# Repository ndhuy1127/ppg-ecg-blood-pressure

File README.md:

# Thiết bị đeo cổ tay ước lượng biến thiên huyết áp từ PPG và ECG

**Thành viên mới:** đọc [Quy trình làm việc GitHub](docs/WORKFLOW.md) trước khi tạo commit hoặc Pull Request.

## Mục tiêu

Dự án xây dựng nguyên mẫu thiết bị đeo cổ tay và pipeline phân tích nhằm nghiên
cứu khả năng ước lượng biến thiên huyết áp giữa các phiên đo từ tín hiệu PPG và
ECG. Sản phẩm hiện chỉ phục vụ nghiên cứu, không phải thiết bị y tế và không
được dùng để chẩn đoán hay đưa ra quyết định điều trị.

## Câu hỏi nghiên cứu

Chi tiết trong
[docs/research_questions_v0.1.md](docs/research_questions_v0.1.md):

1. **RQ1 (câu hỏi chính):** Sau khi hiệu chuẩn bằng một lần đo cuff, việc bổ
   sung ECG để tính PAT có làm giảm sai số dự đoán ΔSBP và ΔDBP ở các phiên đo
   sau so với mô hình chỉ dùng PPG hay không?
2. **RQ2:** Sai số thay đổi bao nhiêu khi chuyển từ chia ngẫu nhiên theo cửa sổ
   (có rò rỉ dữ liệu) sang chia theo người và chia theo phiên đo?
3. **RQ3:** Từ chối dự đoán dựa trên SQI và độ bất định có cho sai số thấp hơn
   so với từ chối ngẫu nhiên ở cùng tỷ lệ giữ lại (coverage) không?

Trong dự án này, **PAT (Pulse Arrival Time)** là thời gian từ đỉnh R của ECG đến
chân sóng PPG. PAT gồm cả thời gian tiền tống máu (PEP), `PAT = PEP + PTT`, nên
**không được gọi là PTT**.

## Thành viên và trách nhiệm

| Thành viên | Trách nhiệm |
| --- | --- |
| Linh | Phần mềm, dữ liệu, mô hình, kiểm thử và CI |
| Đức Anh | Phần cứng, firmware, BOM, PCB và kiểm thử thiết bị |
| Huy | Xử lý tín hiệu, PAT, thống kê, protocol, tài liệu và bài báo |

Phân công chi tiết xem [docs/TEAM.md](docs/TEAM.md).

## Cấu trúc repository

- **configs/**: cấu hình dữ liệu, phần cứng và mô hình.
- **data/**: hướng dẫn quản lý dữ liệu và dữ liệu mẫu nhỏ đã ẩn danh.
- **docs/**: quy trình, kế hoạch, tài liệu nghiên cứu, protocol và đạo đức.
- **hardware/**: BOM, datasheet, sơ đồ nguyên lý, PCB, cơ khí và báo cáo thử.
- **firmware/**: ứng dụng nhúng, driver, board, header và kiểm thử.
- **software/**: nhập dữ liệu, tiền xử lý, xử lý tín hiệu, đặc trưng, mô hình,
  đánh giá và triển khai.
- **notebooks/**: khám phá dữ liệu và thí nghiệm có thể tái lập.
- **scripts/**: công cụ kiểm tra và tác vụ hỗ trợ.
- **tests/**: kiểm thử tự động.
- **reports/**: báo cáo tuần, hình và bản thảo bài báo.

## Cài đặt môi trường

Bắt buộc dùng **Python 3.11**: `pyproject.toml` khai báo
`requires-python = ">=3.11,<3.12"` và CI chạy Python 3.11. Có thể dùng một
trong hai cách:

### pip

Windows PowerShell (`py -3.11` chọn đúng Python 3.11 khi máy có nhiều bản):

~~~powershell
py -3.11 -m venv .venv
.\.venv\Scripts\Activate.ps1
python -m pip install --upgrade pip
python -m pip install -r requirements.txt
~~~

Linux/macOS:

~~~bash
python3.11 -m venv .venv
source .venv/bin/activate
python -m pip install --upgrade pip
python -m pip install -r requirements.txt
~~~

### Conda

~~~text
conda env create -f environment.yml
conda activate ppg-ecg-env
~~~

`requirements.txt`, `pyproject.toml` và `environment.yml` cố định phiên bản
`mat73==0.65` (reader PulseDB), `h5py==3.16.0` (đọc từng phần file `.mat` v7.3, thêm
2026-10-24), `pyserial==3.5` (logger đọc cổng serial, thêm 2026-10-24) và
`xgboost==3.2.0` (baseline B3). PyTorch chưa có
trong dependency; thành viên cần dùng sẽ bổ sung kèm phiên bản cố định.

## Chạy kiểm tra

Từ thư mục gốc của repository, sau khi kích hoạt môi trường:

~~~text
ruff check .
pytest -q
python scripts/check_environment.py
python -m pip check
~~~

## Quy trình nhánh

Luồng tích hợp:

~~~text
dev/thanh-vien → develop → main
~~~

Mỗi người đồng bộ từ **develop**, làm việc trên nhánh cá nhân, tạo pull request
vào **develop** và chờ CI thành công. Chỉ tích hợp **develop** vào
**main** tại một mốc ổn định. Không làm việc trực tiếp trên **main**.

## Dữ liệu và bảo mật

Không commit dữ liệu ECG/PPG thật, dữ liệu định danh, dữ liệu nghiên cứu dung
lượng lớn, bí mật, token hay tệp môi trường. Chỉ dữ liệu mẫu nhỏ và đã ẩn danh
được phép đặt trong **data/sample/**. Dữ liệu nghiên cứu phải dùng
**subject_id**, **session_id** và **event_id**. Xem
[docs/DATA_POLICY.md](docs/DATA_POLICY.md) trước khi thêm dữ liệu.

## Trạng thái dự án

Dự án đang ở tuần 7 trong lộ trình 28 tuần (bắt đầu 2026-09-17; cập nhật 2026-11-10). Tóm tắt theo mức bằng chứng:

| Mức | Nội dung |
| --- | --- |
| Có code và test cục bộ (dữ liệu giả lập) | Reader PulseDB; inventory và split theo người `pulsedb-split-v2`; baseline hằng số B0/B1; MAE/bias/SD; đặc trưng PPG/HR/PAT, SQI `features-sqi-v1` và bootstrap theo người (Tuần 4); pipeline B0/B3 (XGBoost, đặc trưng `pulsedb-simple-stats-v0`) trên split v2, fit trên train và chỉ chấm val ([hướng dẫn](docs/protocol/run_b3_pulsedb.md)); logger packet V0.1 và V0.2 (mốc `SAMP` bit 8, nhiệt độ `0xB1`, cấu hình AFE `0xD2`, lệnh và xác nhận `0xD3`, kênh im lặng), mô phỏng `synthetic-packet-v3`, mốc R/foot thứ hai và quy tắc PAT hợp lệ (Tuần 5) |
| Build được, chưa chạy trên bo | Firmware ESP32-S3 gửi packet V0.2 (`0xD1`, IMU, mốc `SAMP`, nhiệt độ `0xB1`, cấu hình AFE `0xD2`, lệnh từ PC, xung kích thích đồng bộ) từ nguồn AFE giả, và driver chip thật MAX30001, MAX30101, BMI270 chưa chạy trên chip ([firmware/](firmware/README.md)) |
| Đã chạy sơ bộ trên dữ liệu công khai | B0 trên CSV nhãn PulseDB 1.000 đoạn (Tuần 3, lịch sử: tập AAMI Cal đã lộ test, xem [hướng dẫn](docs/protocol/run_b0_pulsedb_csv.md)); B0/B3 trên PulseDB VitalDB Train 400 người, chỉ chấm val, nhãn ABP công khai, không phải cuff ([Tuần 5](reports/weekly/week_05/pulsedb_b3_v1/README.md)); B2 v1 (nhân khẩu học, và thêm HR từ đỉnh R của ECG; [định nghĩa B2](docs/protocol/b2_pulsedb_definition.md)) trên cùng split, chỉ chấm val ngày 2026-11-07, chưa thấy khác biệt so với B0 ([Tuần 6](reports/weekly/week_06/pulsedb_b2_v1/README.md)); B3 chạy ba seed cho cùng kết quả ([theo dõi thí nghiệm](reports/weekly/week_06/experiment_tracking/README.md)). Chưa chấm test |
| Bản thảo | Câu hỏi nghiên cứu, protocol v0.3 ([protocol_outline_v0.2.md](docs/protocol/protocol_outline_v0.2.md)), hồ sơ đạo đức (các mục thiết kế/đạo đức đã có phương án của nhóm ngày 2026-10-29, chờ thầy duyệt trước khi nộp), tổng quan tài liệu, danh sách mua |
| Phần cứng V1, chưa có trong tay | Thiết kế KiCad V1-draft5: PCB V1 đang đặt gia công ở CXT từ 2026-10-28. Bo Waveshare ESP32-S3-DEV-KIT-N8R8-M đã đặt 2026-10-27; các đơn còn lại (DigiKey, kit MAX30001, điện cực, cáp) được báo đã đặt ngày 2026-11-07, ngày giao chưa ghi ([báo cáo Tuần 6](reports/weekly/week_06/README.md)) |
| Chưa có | Phần cứng lắp ráp, bản ghi ECG/PPG của nhóm, dữ liệu cuff, mô hình ΔBP và mọi kết quả trả lời RQ1–RQ3 |

Kết quả trên dữ liệu giả lập chỉ kiểm tra code, không phải hiệu năng ước lượng
huyết áp. Kế hoạch từng tuần nằm trong [docs/plans/](docs/plans/README.md); trạng
thái và bằng chứng nằm trong báo cáo tuần tại [reports/weekly/](reports/weekly/).

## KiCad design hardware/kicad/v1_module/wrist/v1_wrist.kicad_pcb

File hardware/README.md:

# Phần cứng

- **bom/**: danh mục linh kiện và phương án thay thế;
  [danh sách mua V1-module](bom/purchase_list_v1_module.md).
- **datasheets/**: liên kết datasheet chính thức và mức độ đối chiếu thông số
  ([README](datasheets/README.md)); không lưu file PDF.
- **kicad/**: thiết kế KiCad của V1-module, gồm `kicad/v1_module/base` (bo đế)
  và `kicad/v1_module/wrist` (bo cổ tay), mỗi bo có `.kicad_sch`, `.kicad_pcb`,
  `.kicad_pro`. PCB lưu theo định dạng KiCad 10.0, schematic theo 9.0: mở
  `.kicad_pcb` bằng KiCad ≥ 10. Mô tả, bảng GPIO và bảng chân cáp:
  [custom_board_proposal.md](../configs/hardware/custom_board_proposal.md) Phần A.
- **schematics/**: sơ đồ nguyên lý và bản xuất; hiện chỉ có `.gitkeep`.
- **pcb/**: nguồn thiết kế PCB; output và Gerber được Git bỏ qua. Hiện chỉ có
  `.gitkeep`; PCB của V1-module nằm ở `kicad/`.
- **mechanical/**: thiết kế cơ khí và ràng buộc kích thước.
- **test_reports/**: kế hoạch và báo cáo kiểm thử thiết bị:
  - [v1_bringup_procedure.md](test_reports/v1_bringup_procedure.md): trình tự
    kiểm khi nhận hàng, sửa module, hàn, cấp nguồn và kiểm từng khối của V1-module;
  - [sync_10min_test_plan.md](test_reports/sync_10min_test_plan.md): đo tốc độ
    thực, drift, jitter, độ trễ và lệch ECG–PPG khi thử trên bàn với PCB V1 (không
    người), sau bring-up mục 7–8.

Tài liệu cấu hình liên quan ở `configs/hardware/`: yêu cầu V0,
[sơ đồ khối V1-module](../configs/hardware/hardware_diagram_v1.svg),
[nguồn/giao tiếp/lấy mẫu](../configs/hardware/interface_power_sampling_v0.md),
[ước lượng dòng so với cổng USB](../configs/hardware/power_budget_v1.md),
[V1 dùng module và bản chip trần](../configs/hardware/custom_board_proposal.md) và
packet schema [V0.1](../configs/hardware/Packet_Schema_V0.1.md) và bản sửa đổi
[V0.2](../configs/hardware/Packet_Schema_V0.2.md) mà firmware V1 dùng.

Mọi quyết định mua linh kiện phải được duyệt. Tài liệu ở đây không chứng nhận
thiết bị đạt chuẩn y tế.

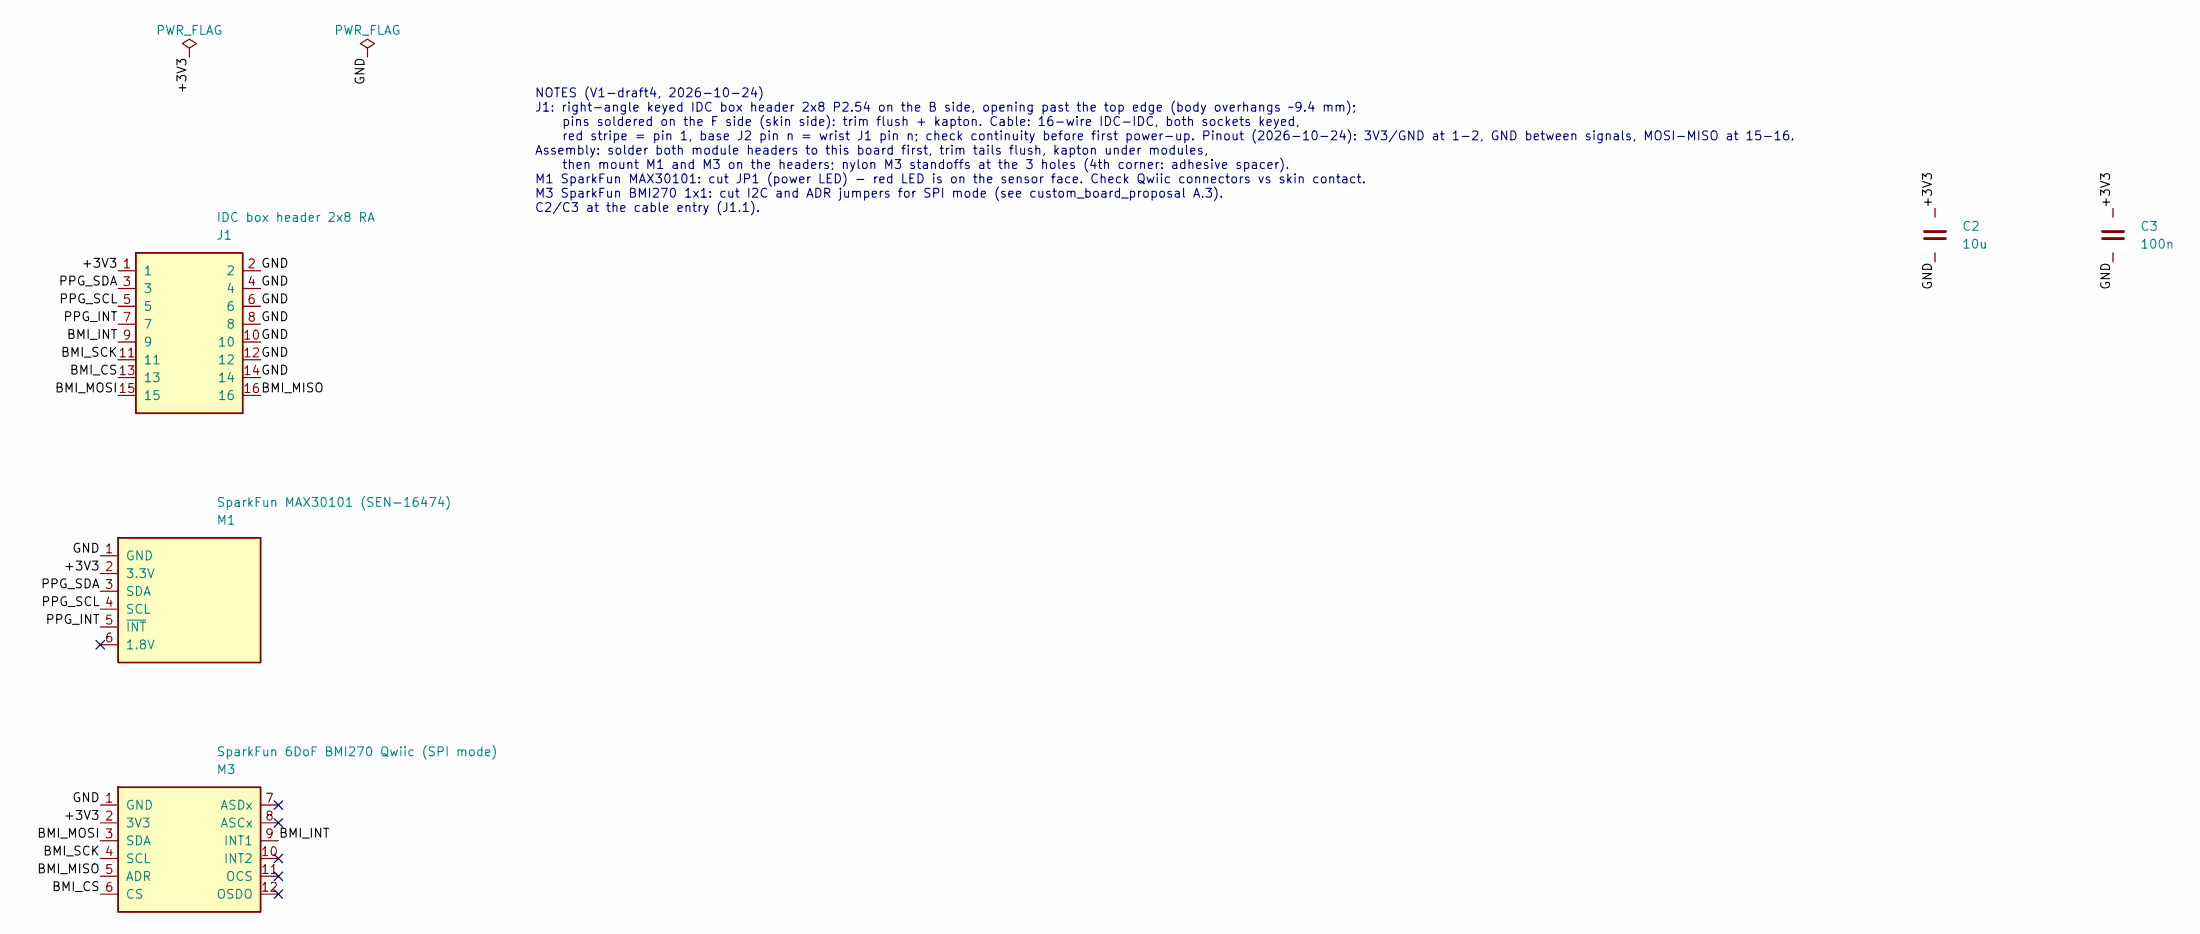
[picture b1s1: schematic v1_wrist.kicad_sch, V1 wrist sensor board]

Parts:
C2: 10u; C_0805_2012Metric
C3: 100n; C_0805_2012Metric
J1: IDC box header 2x8 RA; IDC-Header_2x08_P2.54mm_Horizontal
M1: SparkFun MAX30101 (SEN-16474); SparkFun_MAX30101_Qwiic_Socket
M3: SparkFun 6DoF BMI270 Qwiic (SPI mode); SparkFun_BMI270_Qwiic_Socket

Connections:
/+3V3: C2.1, C3.1, J1.1, M1.2 (3.3V), M3.2 (3V3)
/BMI_CS: J1.13, M3.6 (CS)
/BMI_INT: J1.9, M3.9 (INT1)
/BMI_MISO: J1.16, M3.5 (ADR)
/BMI_MOSI: J1.15, M3.3 (SDA)
/BMI_SCK: J1.11, M3.4 (SCL)
/GND: C2.2, C3.2, J1.2, J1.4, J1.6, J1.8, J1.10, J1.12, J1.14, M1.1 (GND), M3.1 (GND)
/PPG_INT: J1.7, M1.5 (INT)
/PPG_SCL: J1.5, M1.4 (SCL)
/PPG_SDA: J1.3, M1.3 (SDA)

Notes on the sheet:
NOTES (V1-draft4, 2026-10-24) J1: right-angle keyed IDC box header 2x8 P2.54 on the B side, opening past the top edge (body overhangs ~9.4 mm); pins soldered on the F side (skin side): trim flush + kapton. Cable: 16-wire IDC-IDC, both sockets keyed, red stripe = pin 1, base J2 pin n = wrist J1 pin 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

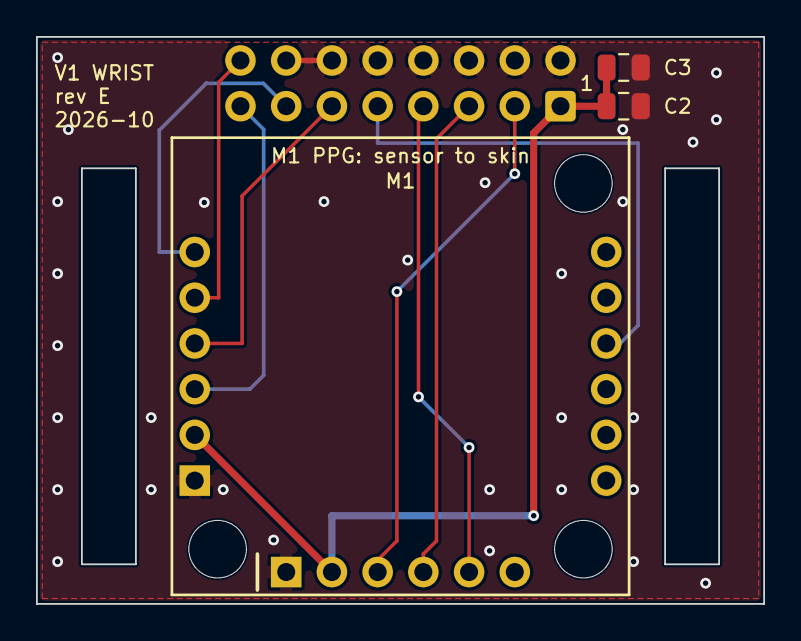
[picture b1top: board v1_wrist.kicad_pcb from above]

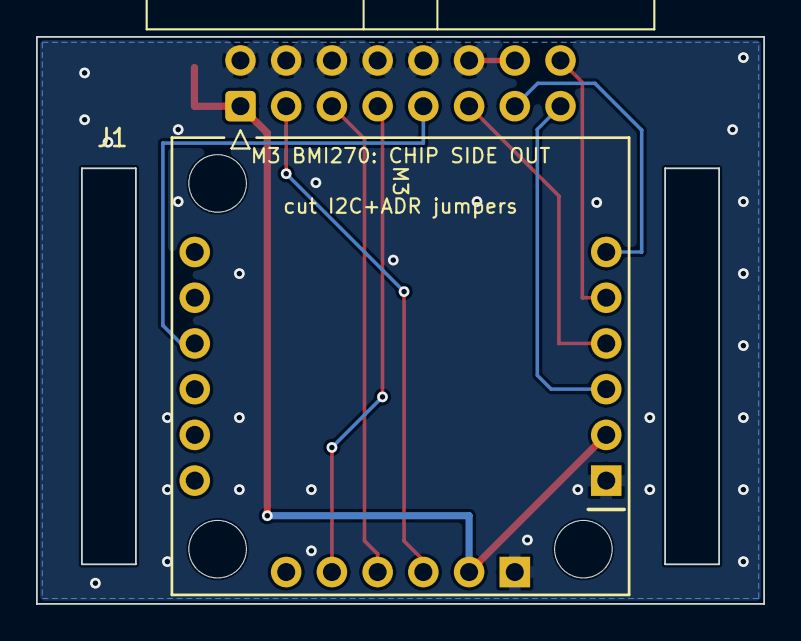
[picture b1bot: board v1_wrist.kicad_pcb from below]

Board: 2 copper layers, 40.4 x 31.5 mm, 5 parts (2 on the bottom side), 10 nets.

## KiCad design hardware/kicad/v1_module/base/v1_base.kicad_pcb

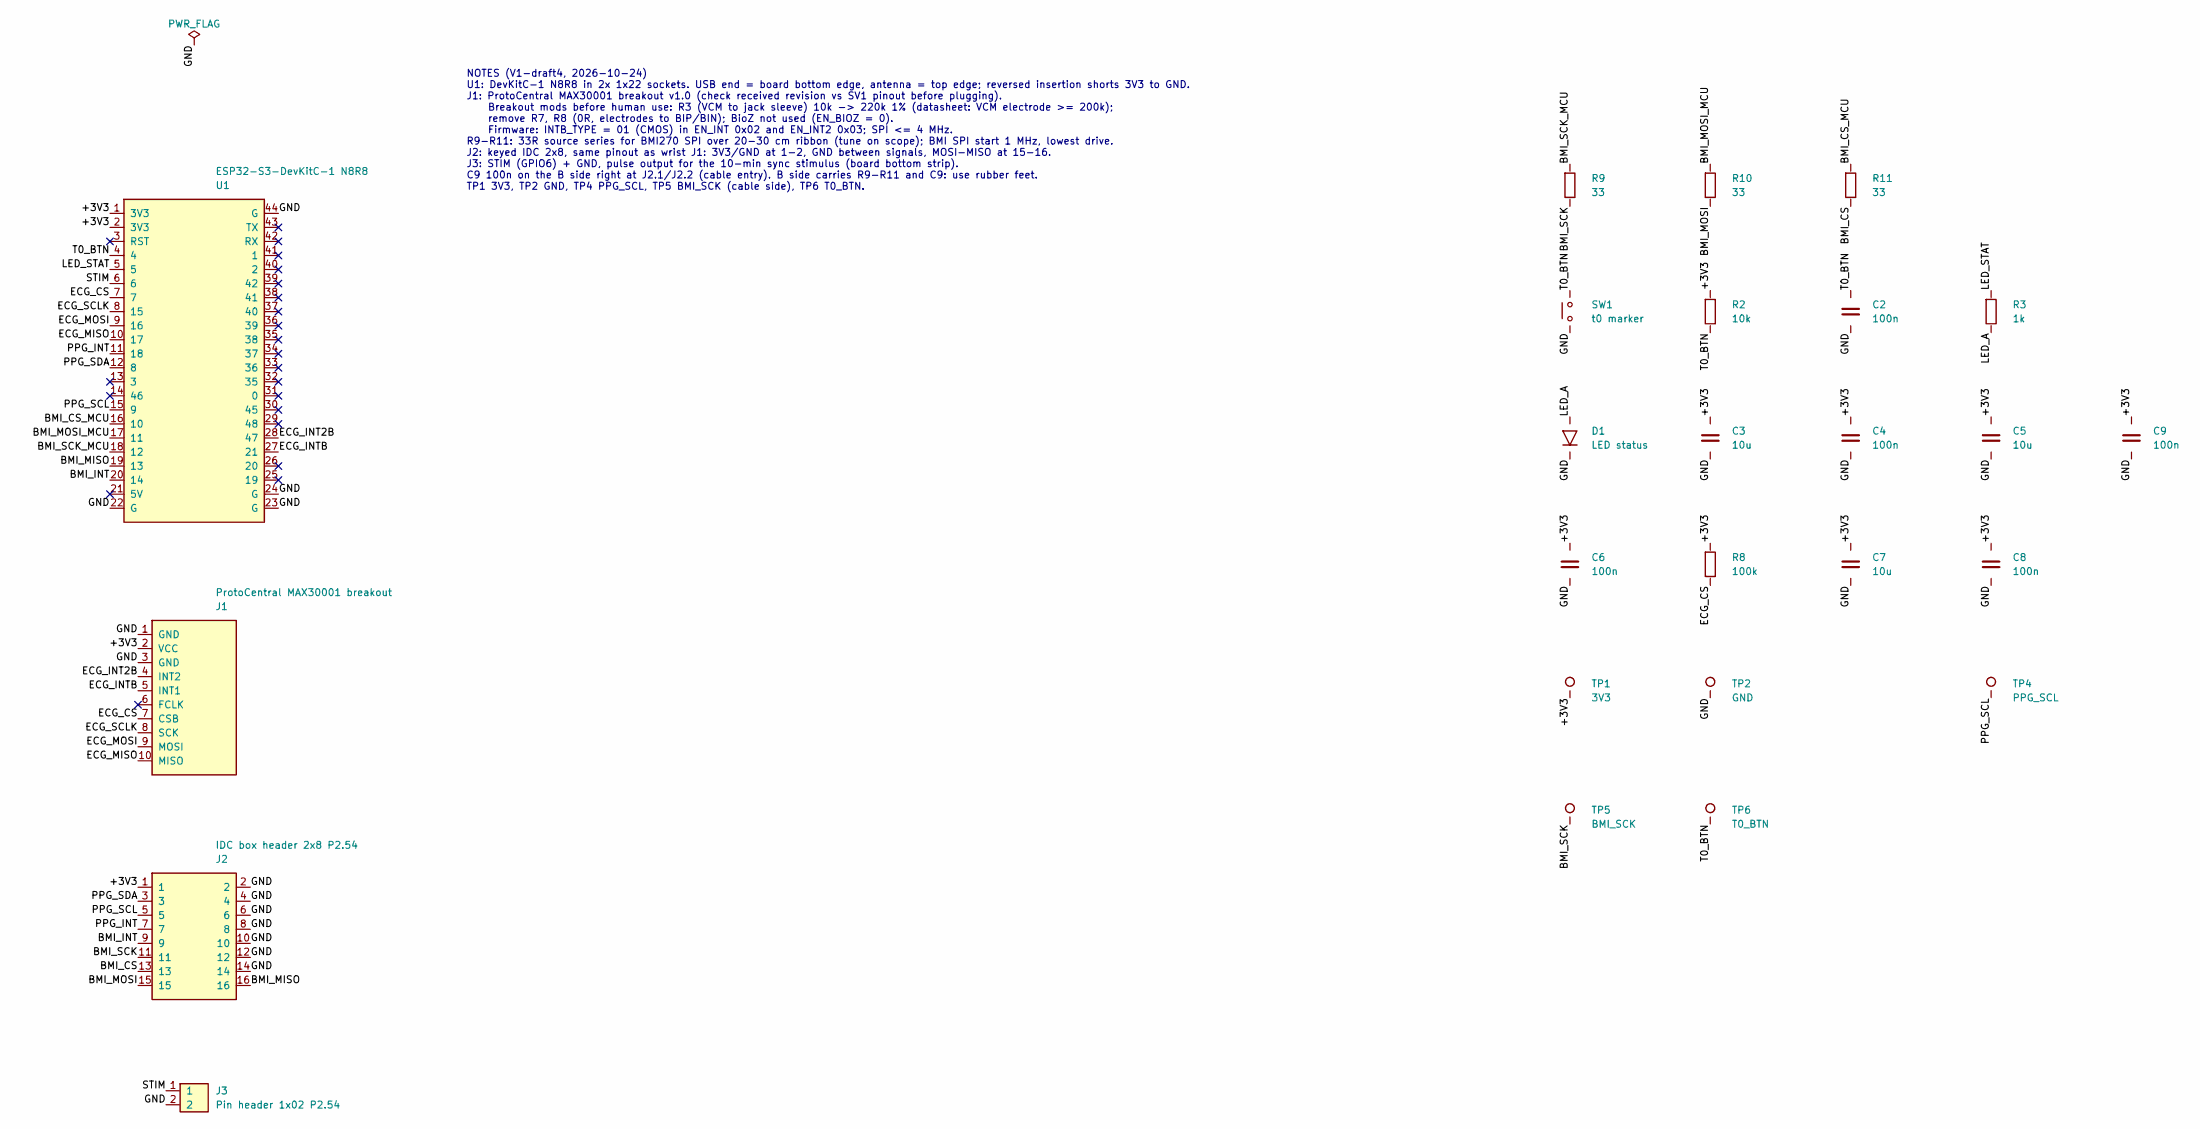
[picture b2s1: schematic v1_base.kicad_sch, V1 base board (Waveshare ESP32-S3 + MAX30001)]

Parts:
C2, C4, C6, C8, C9: 100n; C_0805_2012Metric
C3, C5, C7: 10u; C_0805_2012Metric
D1: LED status; LED_D3.0mm
J1: ProtoCentral MAX30001 breakout; ProtoCentral_MAX30001_BRK_Socket
J2: IDC box header 2x8 P2.54; IDC-Header_2x08_P2.54mm_Vertical
J3: Pin header 1x02 P2.54; PinHeader_1x02_P2.54mm_Vertical
R2: 10k; R_0805_2012Metric
R3: 1k; R_0805_2012Metric
R8: 100k; R_0805_2012Metric
R9, R10, R11: 33; R_0805_2012Metric
SW1: t0 marker; SW_PUSH_6mm
TP1: 3V3; TestPoint_Pad_D1.0mm
TP2: GND; TestPoint_Pad_D1.0mm
TP4: PPG_SCL; TestPoint_Pad_D1.0mm
TP5: BMI_SCK; TestPoint_Pad_D1.0mm
TP6: T0_BTN; TestPoint_Pad_D1.0mm
U1: ESP32-S3-DevKitC-1 N8R8; ESP32-S3-DevKitC-1_Socket

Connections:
/+3V3: C3.1, C4.1, C5.1, C6.1, C7.1, C8.1, C9.1, J1.2 (VCC), J2.1, R2.1, R8.1, TP1.1, U1.1 (3V3), U1.2 (3V3)
/BMI_CS: J2.13, R11.2
/BMI_CS_MCU: R11.1, U1.16 (10)
/BMI_INT: J2.9, U1.20 (14)
/BMI_MISO: J2.16, U1.19 (13)
/BMI_MOSI: J2.15, R10.2
/BMI_MOSI_MCU: R10.1, U1.17 (11)
/BMI_SCK: J2.11, R9.2, TP5.1
/BMI_SCK_MCU: R9.1, U1.18 (12)
/ECG_CS: J1.7 (CSB), R8.2, U1.7
/ECG_INT2B: J1.4 (INT2), U1.28 (47)
/ECG_INTB: J1.5 (INT1), U1.27 (21)
/ECG_MISO: J1.10 (MISO), U1.10 (17)
/ECG_MOSI: J1.9 (MOSI), U1.9 (16)
/ECG_SCLK: J1.8 (SCK), U1.8 (15)
/GND: C2.2, C3.2, C4.2, C5.2, C6.2, C7.2, C8.2, C9.2, D1.1 (K), J1.1 (GND), J1.3 (GND), J2.2, J2.4, J2.6, J2.8, J2.10, J2.12, J2.14, J3.2, SW1.2, TP2.1, U1.22 (G), U1.23 (G), U1.24 (G), U1.44 (G)
/LED_A: D1.2 (A), R3.2
/LED_STAT: R3.1, U1.5
/PPG_INT: J2.7, U1.11 (18)
/PPG_SCL: J2.5, TP4.1, U1.15 (9)
/PPG_SDA: J2.3, U1.12 (8)
/STIM: J3.1, U1.6
/T0_BTN: C2.1, R2.2, SW1.1, TP6.1, U1.4

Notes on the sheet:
NOTES (V1-draft4, 2026-10-24) U1: DevKitC-1 N8R8 in 2x 1x22 sockets. USB end = board bottom edge, antenna = top edge; reversed insertion shorts 3V3 to GND. J1: ProtoCentral MAX30001 breakout v1.0 (check received revision vs SV1 pinout before plugging). Breakout mods before human use: R3 (VCM to jac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

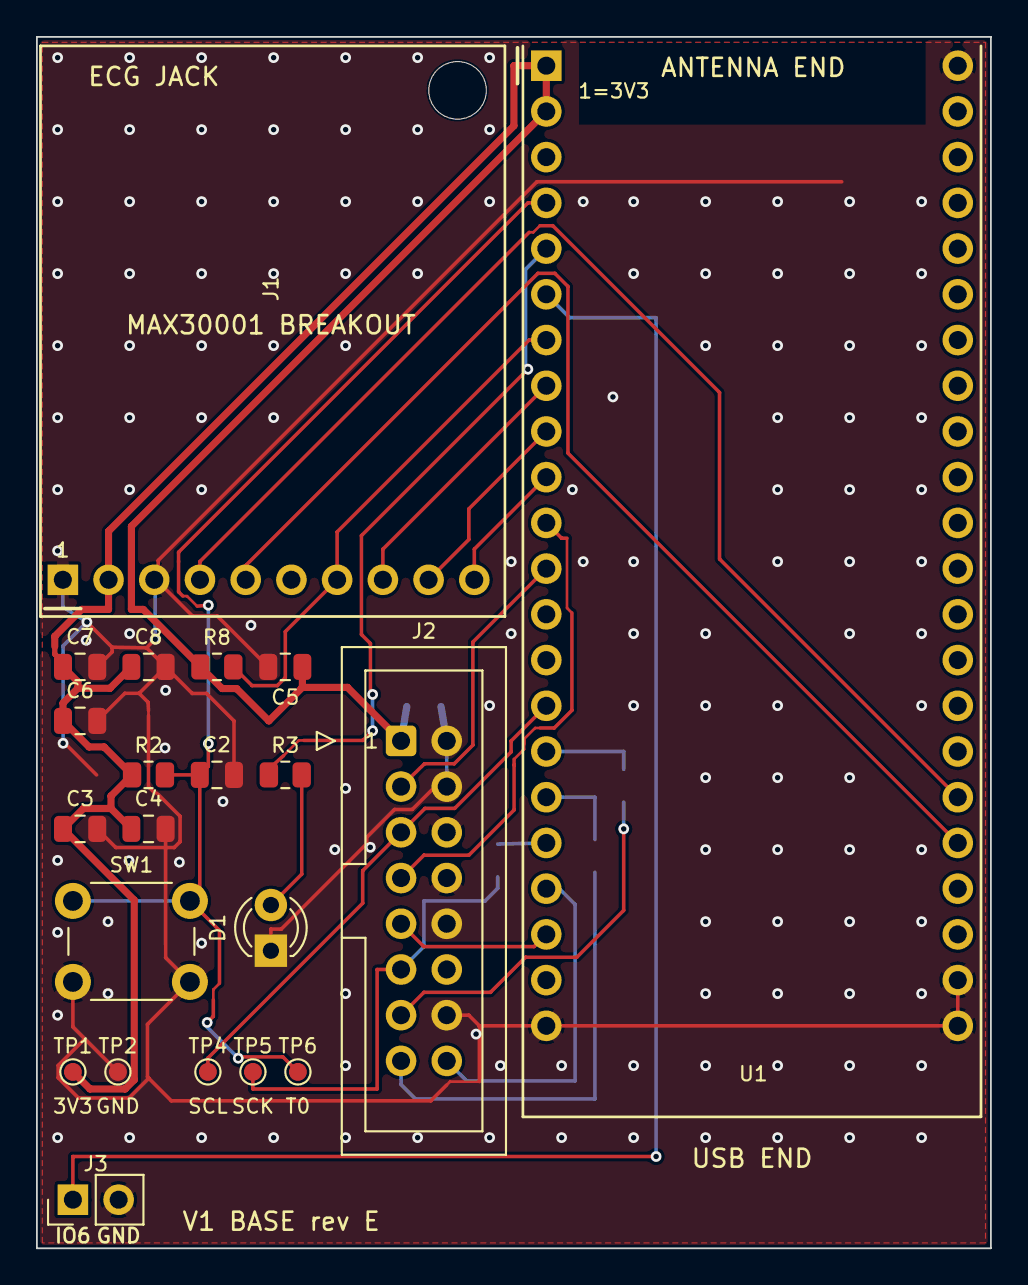
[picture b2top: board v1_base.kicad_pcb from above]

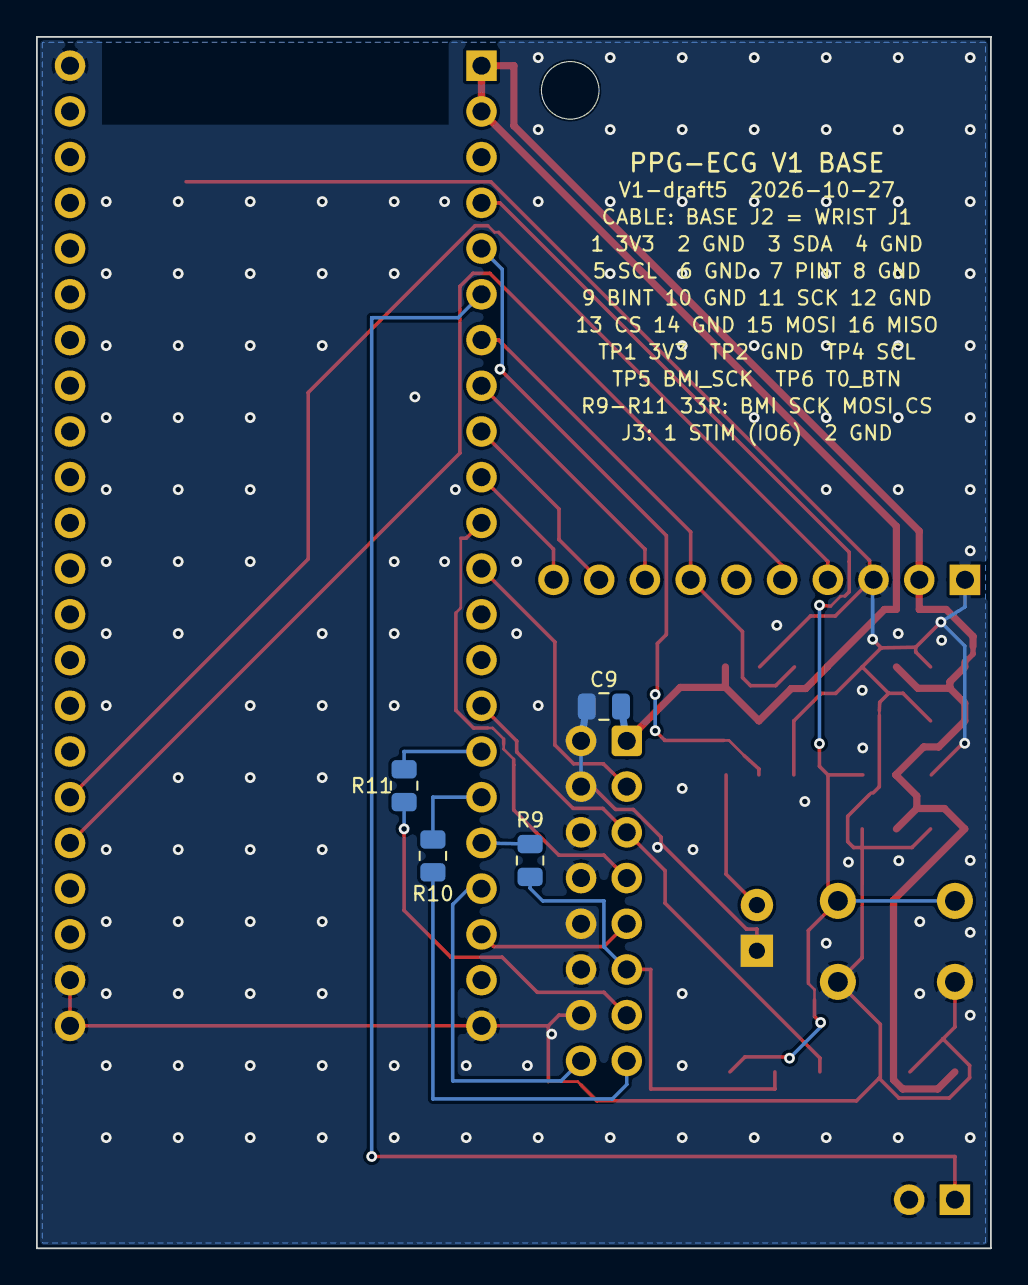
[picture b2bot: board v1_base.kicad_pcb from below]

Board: 2 copper layers, 53.0 x 67.3 mm, 25 parts (4 on the bottom side), 23 nets.
